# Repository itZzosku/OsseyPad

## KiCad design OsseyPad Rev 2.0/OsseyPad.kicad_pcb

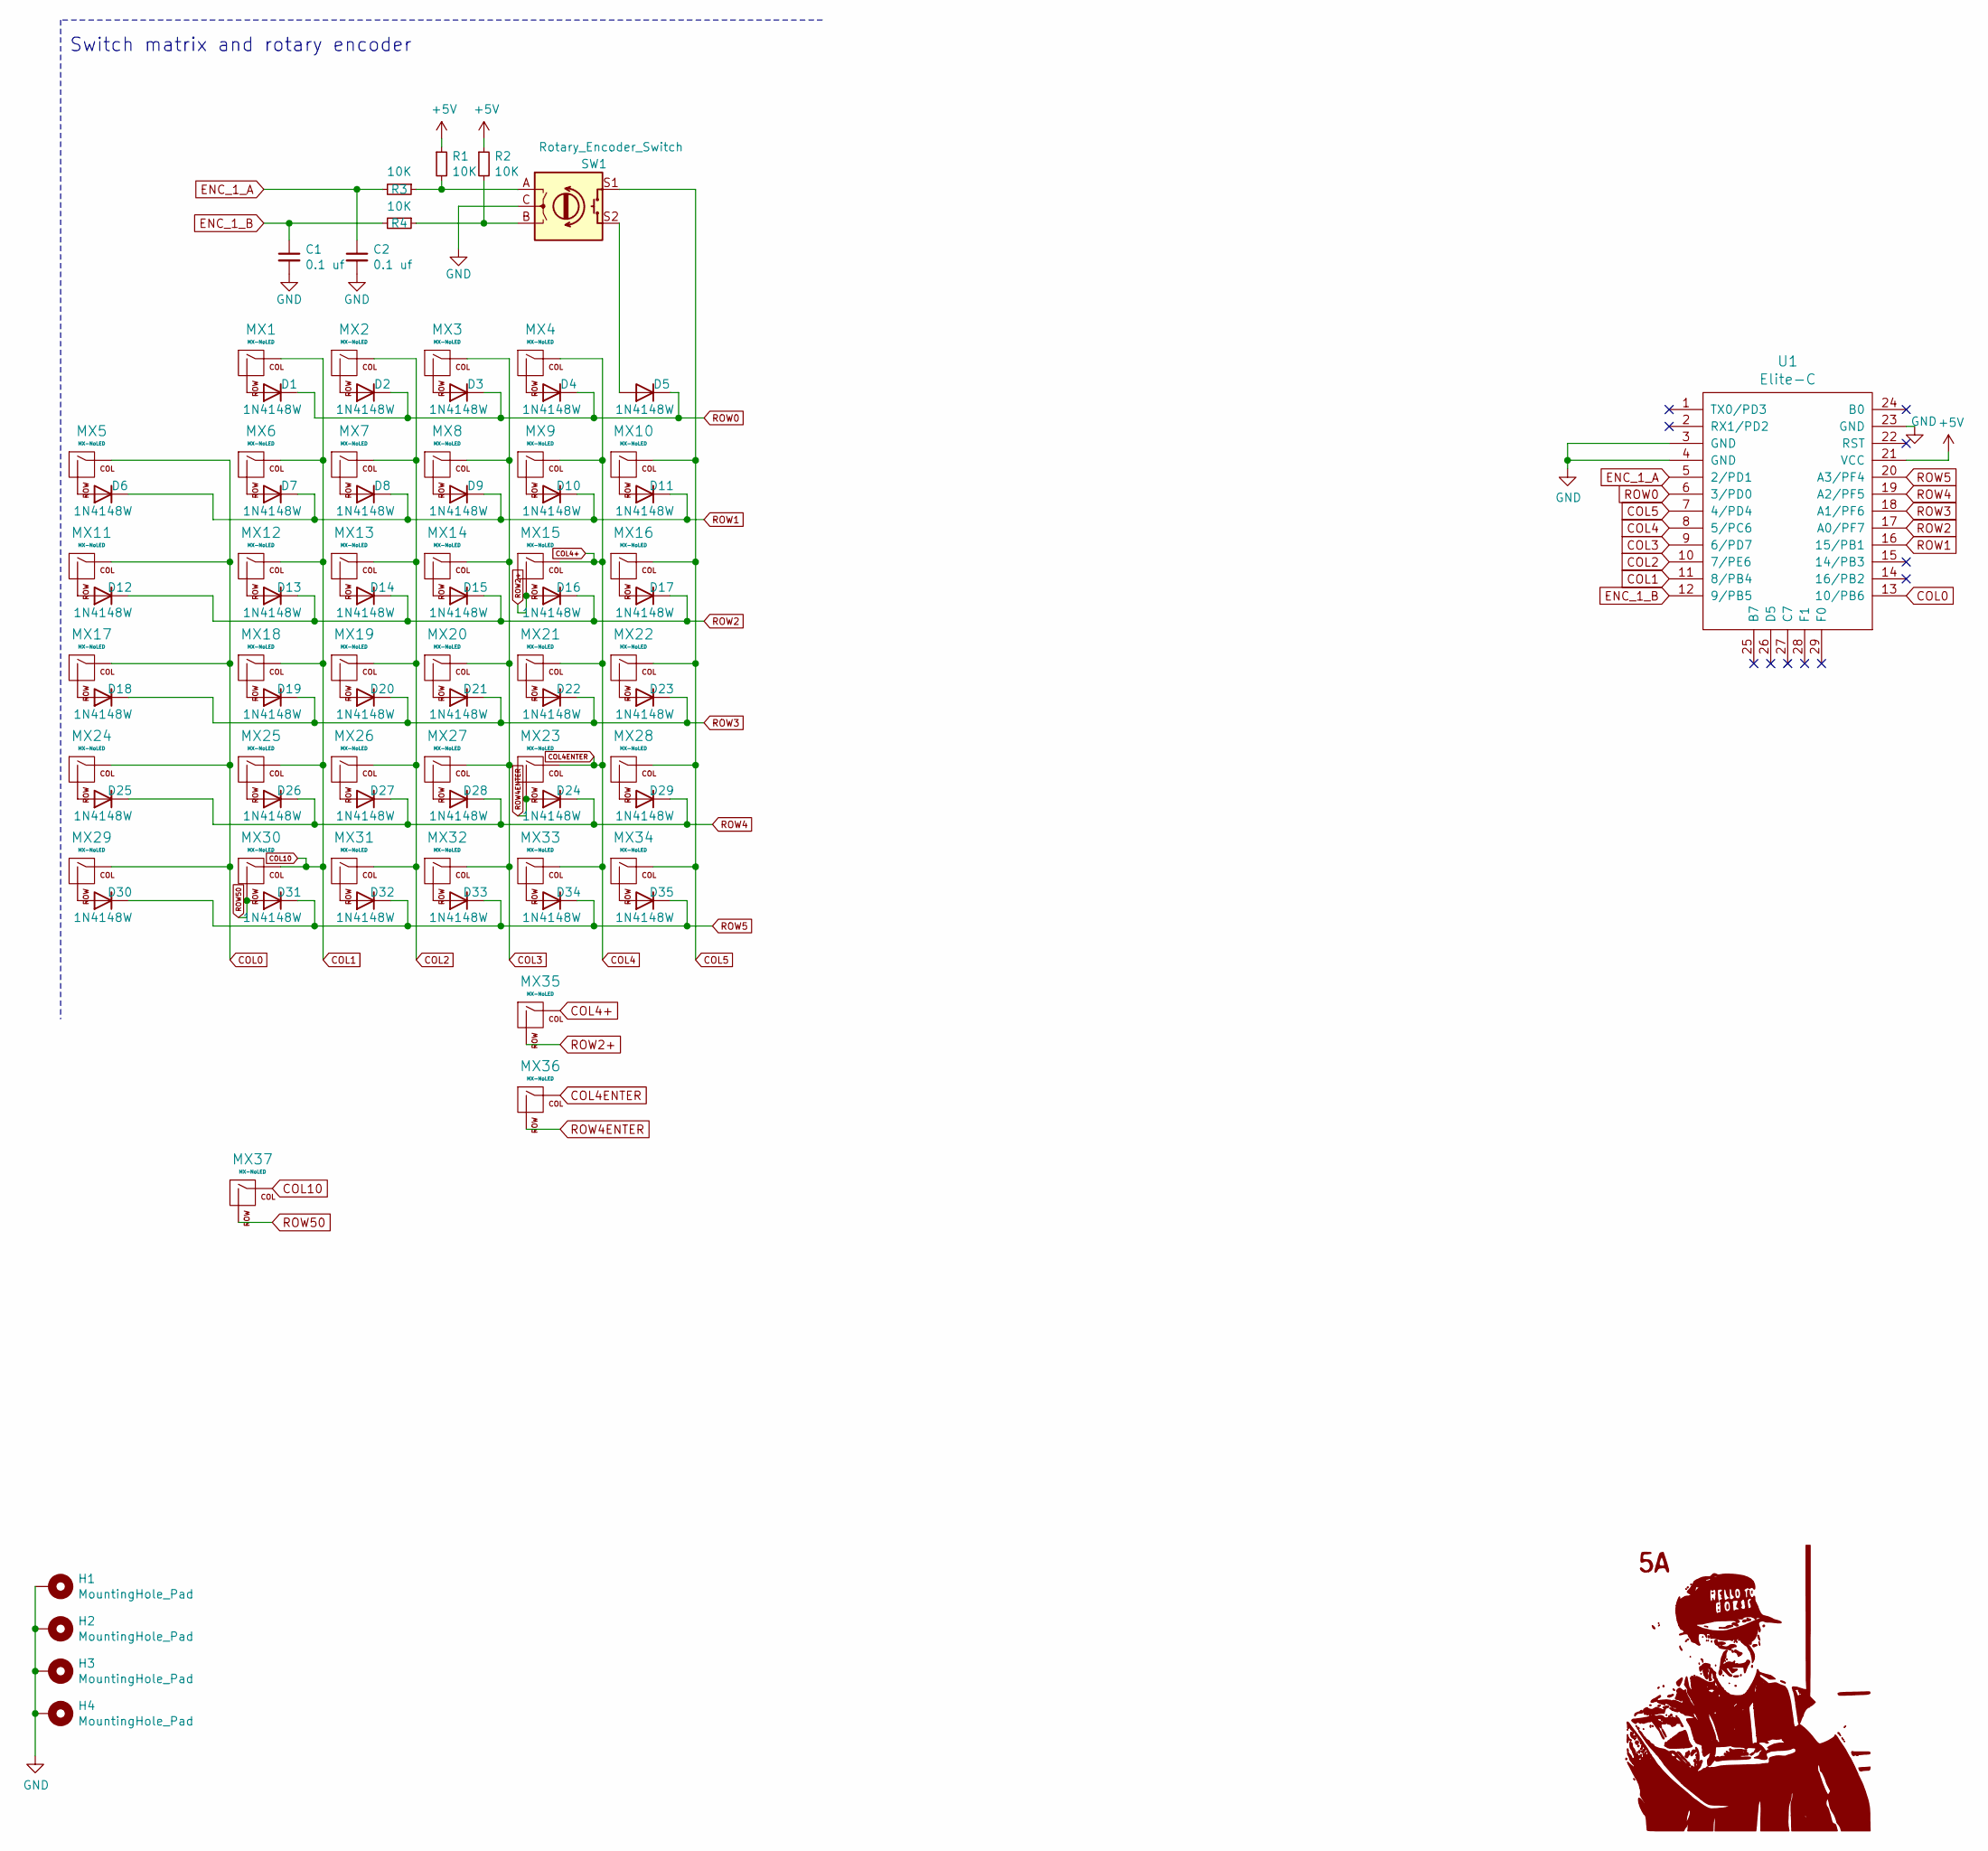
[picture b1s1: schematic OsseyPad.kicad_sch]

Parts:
C1, C2: 0.1 uf; C_Disc_D3.0mm_W2.0mm_P2.50mm
D1, D2, D3, D4, D5, D6, D7, D8, D9, D10, D11, D12, D13, D14, D15, D16, D17, D18, D19, D20, D21, D22, D23, D24, D25, D26, D27, D28, D29, D30, D31, D32, D33, D34, D35: 1N4148W; D_DO-35_SOD27_P7.62mm_Horizontal
H1, H2, H3, H4: MountingHole_Pad; MountingHole_4.3mm_M4_Pad_Via
MX1, MX2, MX3, MX4, MX5, MX6, MX7, MX8, MX9, MX10, MX11, MX12, MX13, MX14, MX15, MX16, MX17, MX18, MX19, MX20, MX21, MX22, MX23, MX24, MX25, MX26, MX27, MX28, MX29, MX30, MX31, MX32, MX33, MX34: MX-NoLED; MXOnly-1U-NoLED_Edit1
MX35, MX36, MX37: MX-NoLED; MXOnly-2U-NoLED
R1, R2, R3, R4: 10K; R_Axial_DIN0309_L9.0mm_D3.2mm_P12.70mm_Horizontal
SW1: Rotary_Encoder_Switch; RotaryEncoder_Alps_EC11E-Switch_Vertical_H20mm_CircularMoun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
U1: Elite-C; Elite-C-castellated-29pin-holes_Edit1

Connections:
+5V: R1.1, R2.1, U1.21 (VCC)
COL0: MX5.1 (COL), MX11.1 (COL), MX17.1 (COL), MX24.1 (COL), MX29.1 (COL), U1.13 (10/PB6)
COL1: MX1.1 (COL), MX6.1 (COL), MX12.1 (COL), MX18.1 (COL), MX25.1 (COL), MX30.1 (COL), MX37.1 (COL), U1.11 (8/PB4)
COL2: MX2.1 (COL), MX7.1 (COL), MX13.1 (COL), MX19.1 (COL), MX26.1 (COL), MX31.1 (COL), U1.10 (7/PE6)
COL3: MX3.1 (COL), MX8.1 (COL), MX14.1 (COL), MX20.1 (COL), MX27.1 (COL), MX32.1 (COL), U1.9 (6/PD7)
COL4: MX4.1 (COL), MX9.1 (COL), MX15.1 (COL), MX21.1 (COL), MX23.1 (COL), MX33.1 (COL), MX35.1 (COL), MX36.1 (COL), U1.8 (5/PC6)
COL5: MX10.1 (COL), MX16.1 (COL), MX22.1 (COL), MX28.1 (COL), MX34.1 (COL), SW1.S1, U1.7 (4/PD4)
ENC_1_A: C2.1, R3.2, U1.5 (2/PD1)
ENC_1_B: C1.1, R4.2, U1.12 (9/PB5)
GND: C1.2, C2.2, H1.1, H2.1, H3.1, H4.1, SW1.C, U1.3 (GND), U1.4 (GND), U1.23 (GND)
unnamed: D1.2 (A), MX1.2 (ROW)
unnamed: D2.2 (A), MX2.2 (ROW)
unnamed: D3.2 (A), MX3.2 (ROW)
unnamed: D4.2 (A), MX4.2 (ROW)
unnamed: D5.2 (A), SW1.S2
unnamed: D6.2 (A), MX5.2 (ROW)
unnamed: D7.2 (A), MX6.2 (ROW)
unnamed: D8.2 (A), MX7.2 (ROW)
unnamed: D9.2 (A), MX8.2 (ROW)
unnamed: D10.2 (A), MX9.2 (ROW)
unnamed: D11.2 (A), MX10.2 (ROW)
unnamed: D12.2 (A), MX11.2 (ROW)
unnamed: D13.2 (A), MX12.2 (ROW)
unnamed: D14.2 (A), MX13.2 (ROW)
unnamed: D15.2 (A), MX14.2 (ROW)
unnamed: D17.2 (A), MX16.2 (ROW)
unnamed: D18.2 (A), MX17.2 (ROW)
unnamed: D19.2 (A), MX18.2 (ROW)
unnamed: D20.2 (A), MX19.2 (ROW)
unnamed: D21.2 (A), MX20.2 (ROW)
unnamed: D22.2 (A), MX21.2 (ROW)
unnamed: D23.2 (A), MX22.2 (ROW)
unnamed: D25.2 (A), MX24.2 (ROW)
unnamed: D26.2 (A), MX25.2 (ROW)
unnamed: D27.2 (A), MX26.2 (ROW)
unnamed: D28.2 (A), MX27.2 (ROW)
unnamed: D29.2 (A), MX28.2 (ROW)
unnamed: D30.2 (A), MX29.2 (ROW)
unnamed: D32.2 (A), MX31.2 (ROW)
unnamed: D33.2 (A), MX32.2 (ROW)
unnamed: D34.2 (A), MX33.2 (ROW)
unnamed: D35.2 (A), MX34.2 (ROW)
unnamed: R1.2, R3.1, SW1.A
unnamed: R2.2, R4.1, SW1.B
ROW0: D1.1 (K), D2.1 (K), D3.1 (K), D4.1 (K), D5.1 (K), U1.6 (3/PD0)
ROW1: D6.1 (K), D7.1 (K), D8.1 (K), D9.1 (K), D10.1 (K), D11.1 (K), U1.16 (15/PB1)
ROW2: D12.1 (K), D13.1 (K), D14.1 (K), D15.1 (K), D16.1 (K), D17.1 (K), U1.17 (A0/PF7)
ROW2+: D16.2 (A), MX15.2 (ROW), MX35.2 (ROW)
ROW3: D18.1 (K), D19.1 (K), D20.1 (K), D21.1 (K), D22.1 (K), D23.1 (K), U1.18 (A1/PF6)
ROW4: D24.1 (K), D25.1 (K), D26.1 (K), D27.1 (K), D28.1 (K), D29.1 (K), U1.19 (A2/PF5)
ROW4ENTER: D24.2 (A), MX23.2 (ROW), MX36.2 (ROW)
ROW5: D30.1 (K), D31.1 (K), D32.1 (K), D33.1 (K), D34.1 (K), D35.1 (K), U1.20 (A3/PF4)
ROW50: D31.2 (A), MX30.2 (ROW), MX37.2 (ROW)

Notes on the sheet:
Switch matrix and rotary encoder

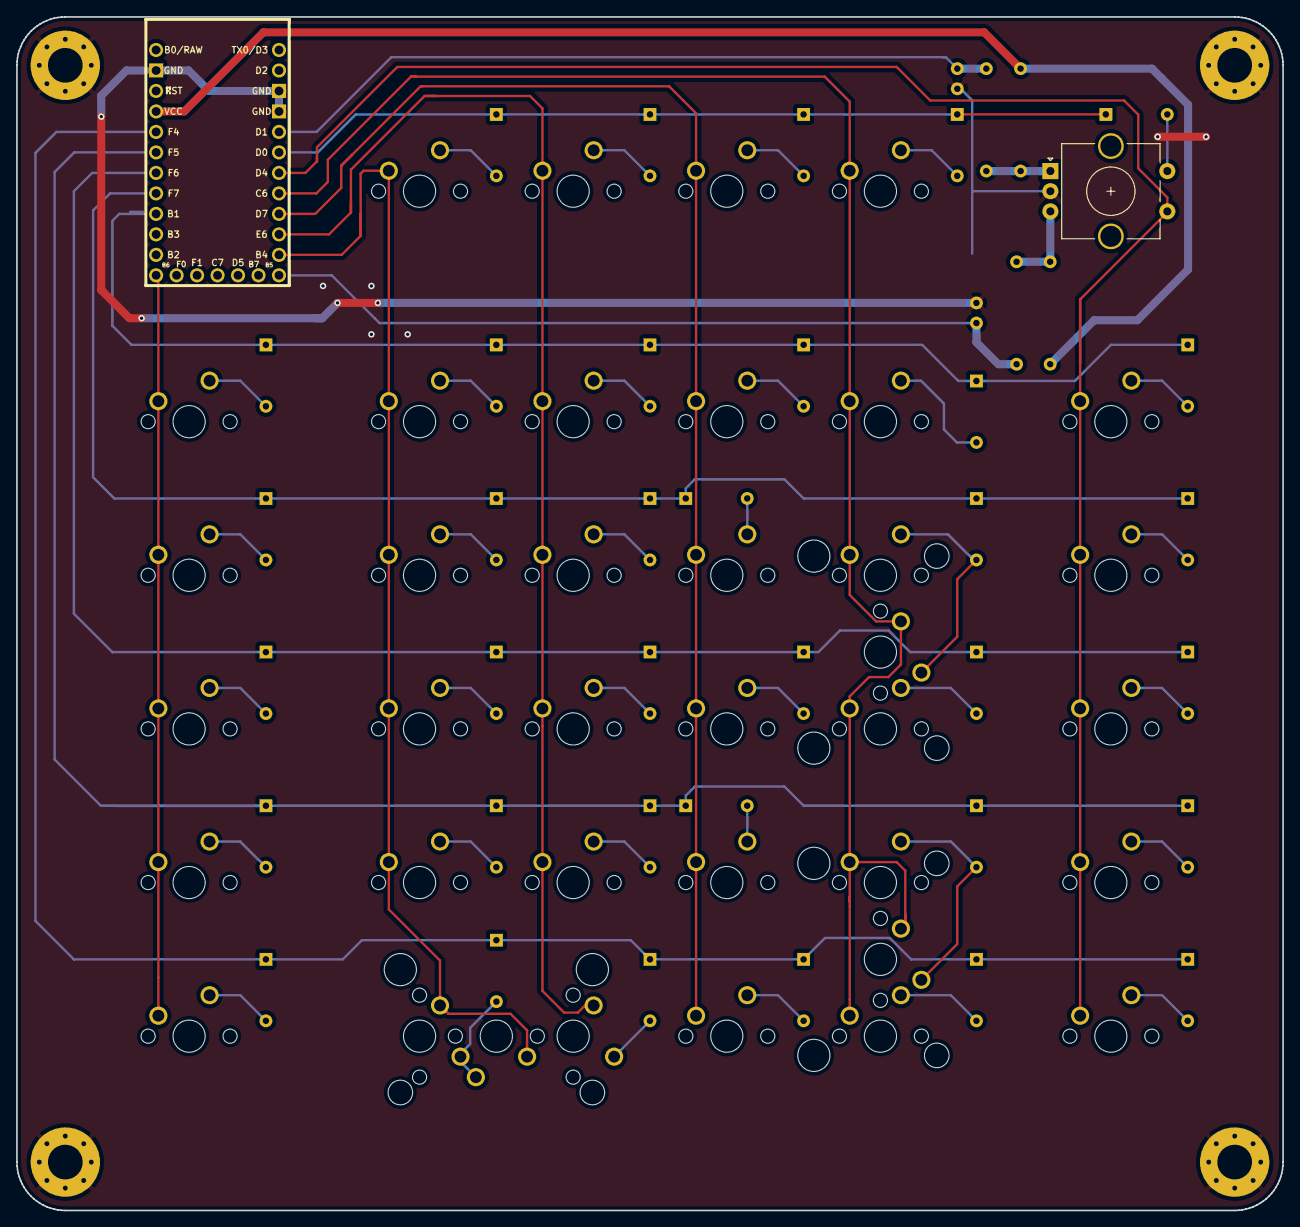
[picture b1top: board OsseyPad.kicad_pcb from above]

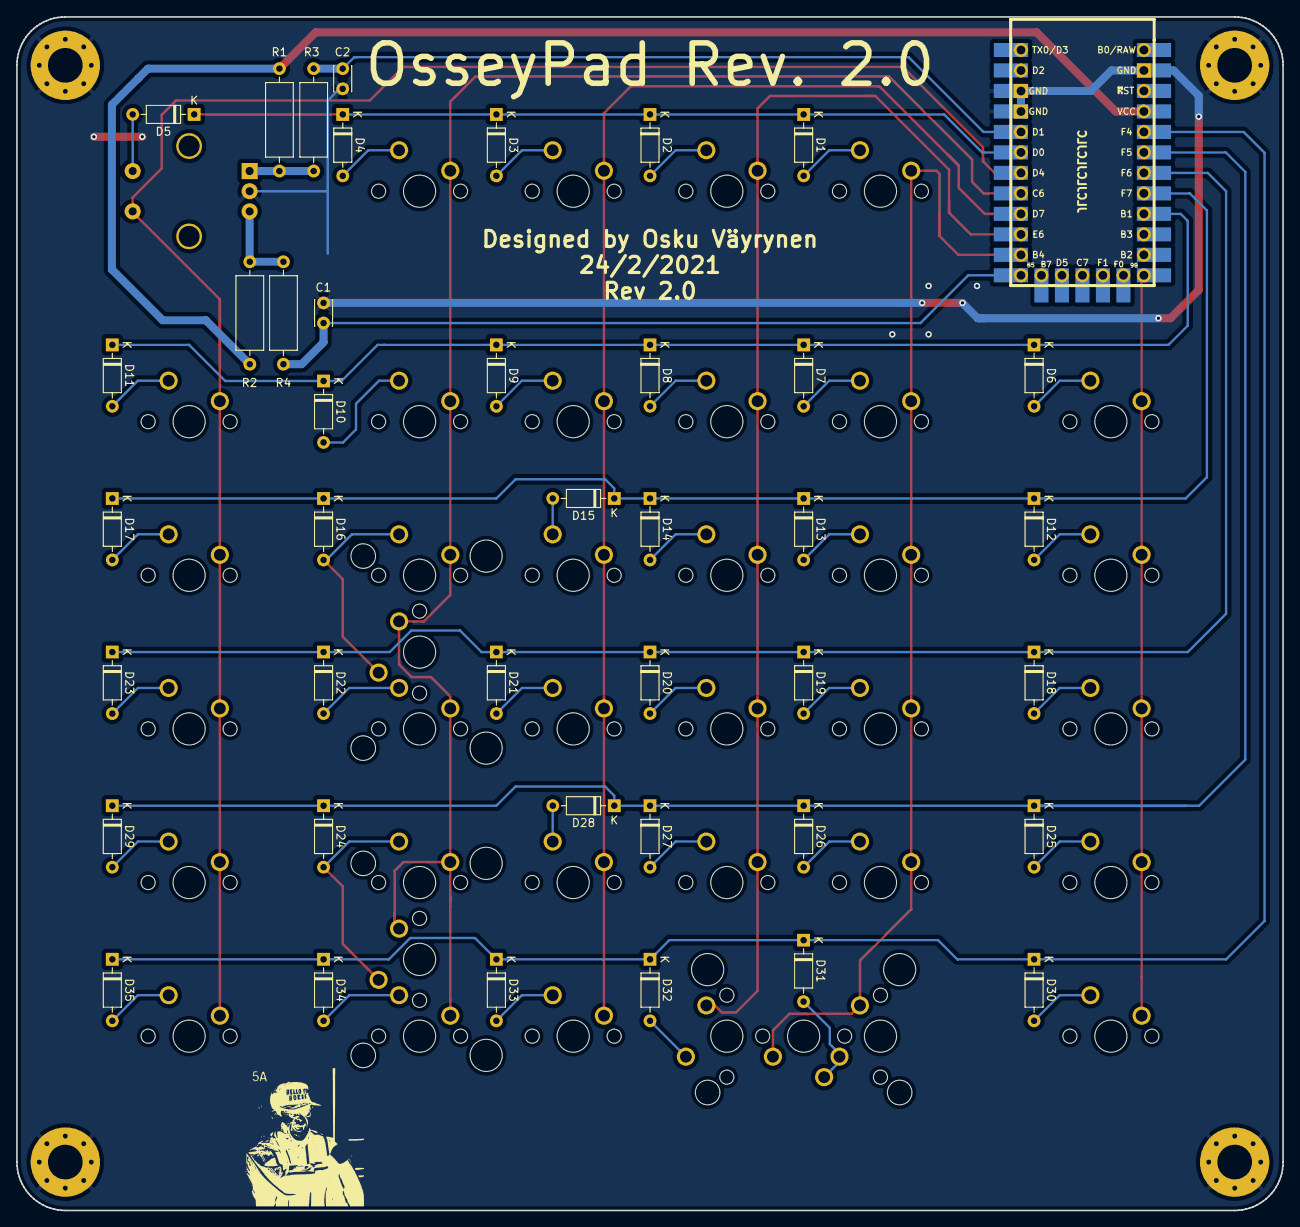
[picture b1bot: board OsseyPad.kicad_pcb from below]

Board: 2 copper layers, 157.0 x 148.0 mm, 84 parts (42 on the bottom side), 53 nets.

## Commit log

2021-01-01 First commit.
2021-01-02 Updated the pcb.
2021-01-03 Updatet the pcb and added first versio off the firmware.
2021-01-06 Updatet the pcb and added models for the case.
2021-01-08 PCB Update.
2021-01-10 Added the JAE_USB_C library.
2021-01-10 Added the Revision 1.1
2021-01-10 Updated the case.
2021-01-16 Updated the case and pcb.
2021-01-21 Updatet the Rev 1.1
2021-01-29 Started to work for OsseyPad 2.0
2021-01-30 Worked on with 2.0
2021-02-03 Worked on Rev 2.0.
2021-02-05 Worked on the pcb design.
2021-02-05 Worked on the firmware. VIA should work now.
2021-02-05 Updated the PCB for rev 2.0.
2021-02-07 Added the keebio libs.
2021-02-08 Worked on pcb and case for 2.0.
2021-02-09 Worked on pcb and case.
2021-02-11 Updated the OsseyPad firmware.
2021-02-11 Refactored firmware.
2021-02-11 Deleted the backups.
2021-02-23 Updated the pcb and case.
2021-02-24 Updated the pcb and made the production files.
